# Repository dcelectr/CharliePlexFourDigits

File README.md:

# CharliePlexFourDigits
Four Digit (5 x 7 + 1dp) LED Matrices for use with the Adafruit 16x9 Charlieplexed PWM LED Matrix Driver - IS31FL3731 (Adafruit Product ID: 2946).
Up to four units can be used on the same I2C bus (addresses 0x74, 0x75, 0x76, and 0x77).

# To do
Arduino library.

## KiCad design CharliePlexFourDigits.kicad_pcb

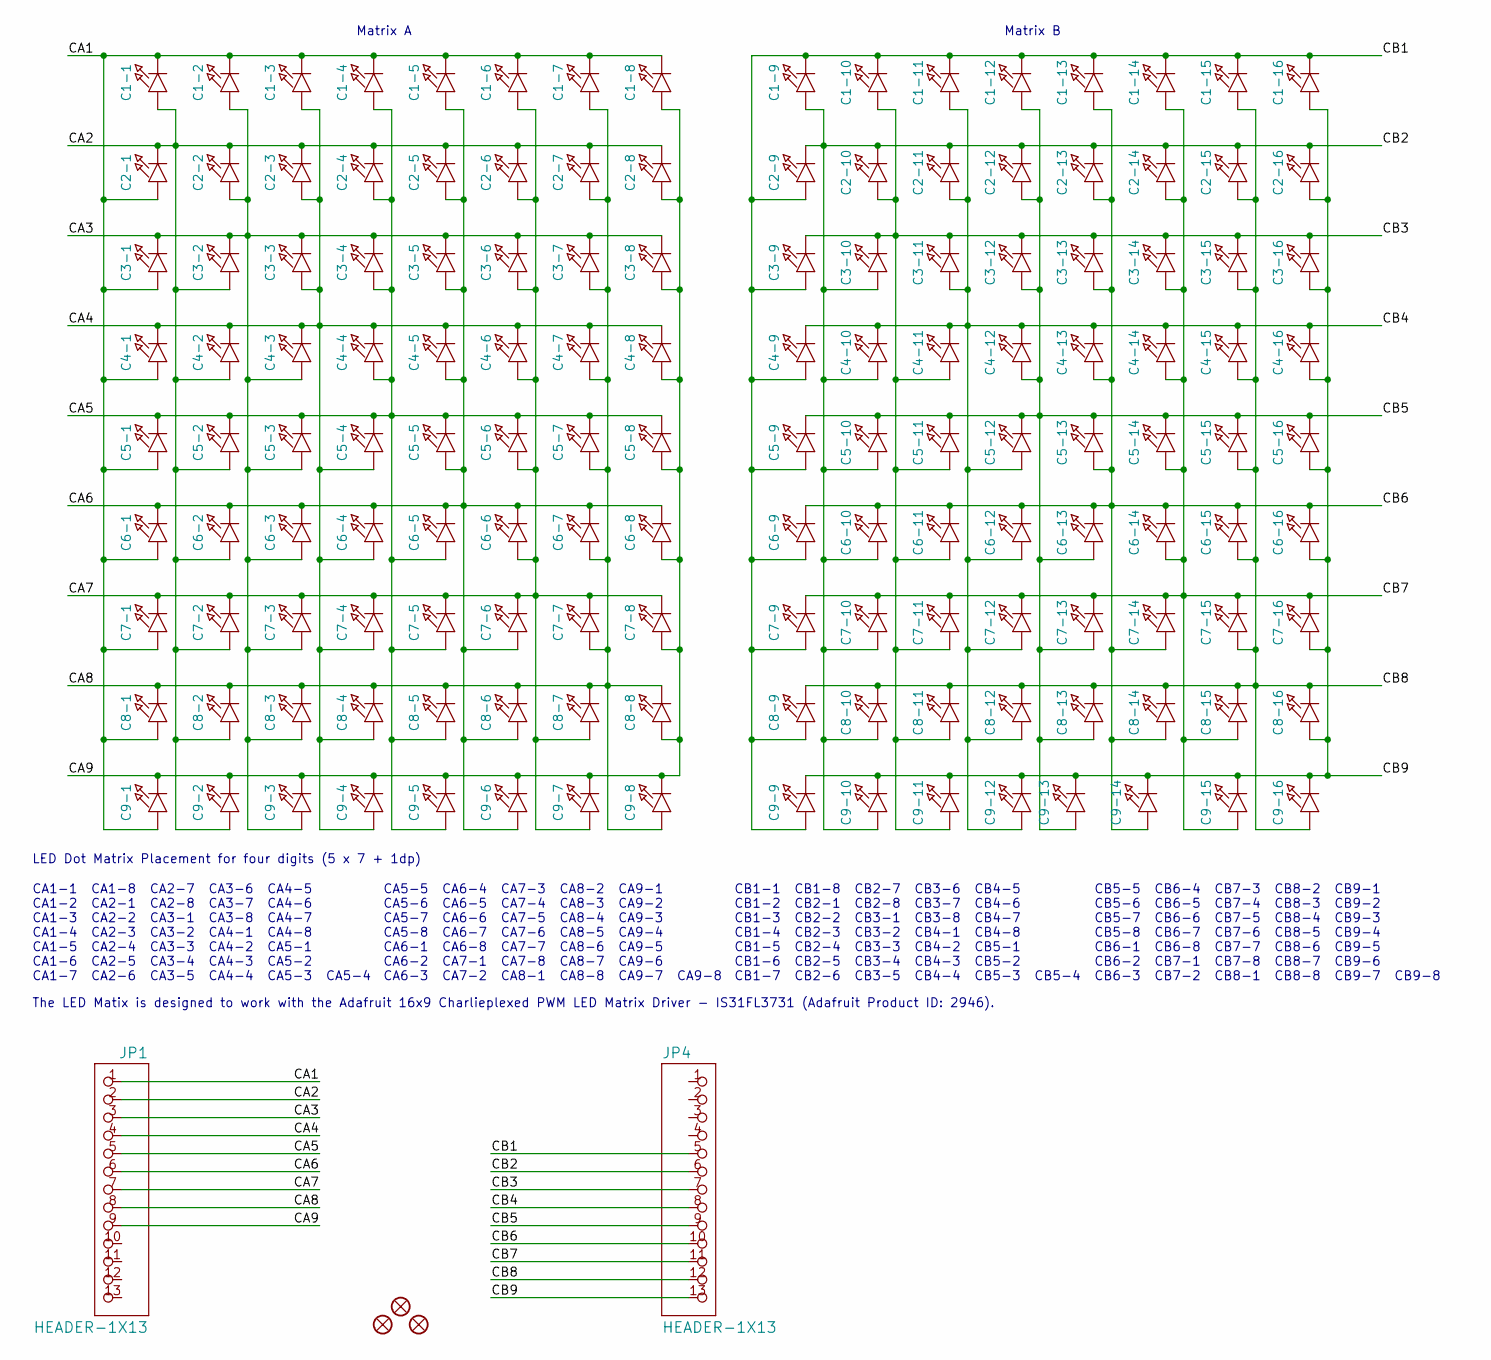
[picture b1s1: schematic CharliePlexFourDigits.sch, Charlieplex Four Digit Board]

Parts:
C1-1, C1-2, C1-3, C1-4, C1-5, C1-6, C1-7, C1-8, C1-9, C1-10, C1-11, C1-12, C1-13, C1-14, C1-15, C1-16, C2-1, C2-2, C2-3, C2-4, C2-5, C2-6, C2-7, C2-8, C2-9, C2-10, C2-11, C2-12, C2-13, C2-14, C2-15, C2-16, C3-1, C3-2, C3-3, C3-4, C3-5, C3-6, C3-7, C3-8, C3-9, C3-10, C3-11, C3-12, C3-13, C3-14, C3-15, C3-16, C4-1, C4-2, C4-3, C4-4, C4-5, C4-6, C4-7, C4-8, C4-9, C4-10, C4-11, C4-12, C4-13, C4-14, C4-15, C4-16, C5-1, C5-2, C5-3, C5-4, C5-5, C5-6, C5-7, C5-8, C5-9, C5-10, C5-11, C5-12, C5-13, C5-14, C5-15, C5-16, C6-1, C6-2, C6-3, C6-4, C6-5, C6-6, C6-7, C6-8, C6-9, C6-10, C6-11, C6-12, C6-13, C6-14, C6-15, C6-16, C7-1, C7-2, C7-3, C7-4, C7-5, C7-6, C7-7, C7-8, C7-9, C7-10, C7-11, C7-12, C7-13, C7-14, C7-15, C7-16, C8-1, C8-2, C8-3, C8-4, C8-5, C8-6, C8-7, C8-8, C8-9, C8-10, C8-11, C8-12, C8-13, C8-14, C8-15, C8-16, C9-1, C9-2, C9-3, C9-4, C9-5, C9-6, C9-7, C9-8, C9-9, C9-10, C9-11, C9-12, C9-13, C9-14, C9-15, C9-16: LED0603_NOOUTLINE; CHIPLED_0603_NOOUTLINE
FID1, FID2, FID3: FIDUCIAL\"\"; FIDUCIAL_1MM
JP1, JP4: HEADER-1X13; 1X13_ROUND_70

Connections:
/CA1: C1-1.C, C1-2.C, C1-3.C, C1-4.C, C1-5.C, C1-6.C, C1-7.C, C1-8.C, C2-1.A, C3-1.A, C4-1.A, C5-1.A, C6-1.A, C7-1.A, C8-1.A, C9-1.A, JP1.1
/CA2: C1-1.A, C2-1.C, C2-2.C, C2-3.C, C2-4.C, C2-5.C, C2-6.C, C2-7.C, C2-8.C, C3-2.A, C4-2.A, C5-2.A, C6-2.A, C7-2.A, C8-2.A, C9-2.A, JP1.2
/CA3: C1-2.A, C2-2.A, C3-1.C, C3-2.C, C3-3.C, C3-4.C, C3-5.C, C3-6.C, C3-7.C, C3-8.C, C4-3.A, C5-3.A, C6-3.A, C7-3.A, C8-3.A, C9-3.A, JP1.3
/CA4: C1-3.A, C2-3.A, C3-3.A, C4-1.C, C4-2.C, C4-3.C, C4-4.C, C4-5.C, C4-6.C, C4-7.C, C4-8.C, C5-4.A, C6-4.A, C7-4.A, C8-4.A, C9-4.A, JP1.4
/CA5: C1-4.A, C2-4.A, C3-4.A, C4-4.A, C5-1.C, C5-2.C, C5-3.C, C5-4.C, C5-5.C, C5-6.C, C5-7.C, C5-8.C, C6-5.A, C7-5.A, C8-5.A, C9-5.A, JP1.5
/CA6: C1-5.A, C2-5.A, C3-5.A, C4-5.A, C5-5.A, C6-1.C, C6-2.C, C6-3.C, C6-4.C, C6-5.C, C6-6.C, C6-7.C, C6-8.C, C7-6.A, C8-6.A, C9-6.A, JP1.6
/CA7: C1-6.A, C2-6.A, C3-6.A, C4-6.A, C5-6.A, C6-6.A, C7-1.C, C7-2.C, C7-3.C, C7-4.C, C7-5.C, C7-6.C, C7-7.C, C7-8.C, C8-7.A, C9-7.A, JP1.7
/CA8: C1-7.A, C2-7.A, C3-7.A, C4-7.A, C5-7.A, C6-7.A, C7-7.A, C8-1.C, C8-2.C, C8-3.C, C8-4.C, C8-5.C, C8-6.C, C8-7.C, C8-8.C, C9-8.A, JP1.8
/CA9: C1-8.A, C2-8.A, C3-8.A, C4-8.A, C5-8.A, C6-8.A, C7-8.A, C8-8.A, C9-1.C, C9-2.C, C9-3.C, C9-4.C, C9-5.C, C9-6.C, C9-7.C, C9-8.C, JP1.9
/CB1: C1-9.C, C1-10.C, C1-11.C, C1-12.C, C1-13.C, C1-14.C, C1-15.C, C1-16.C, C2-9.A, C3-9.A, C4-9.A, C5-9.A, C6-9.A, C7-9.A, C8-9.A, C9-9.A, JP4.5
/CB2: C1-9.A, C2-9.C, C2-10.C, C2-11.C, C2-12.C, C2-13.C, C2-14.C, C2-15.C, C2-16.C, C3-10.A, C4-10.A, C5-10.A, C6-10.A, C7-10.A, C8-10.A, C9-10.A, JP4.6
/CB3: C1-10.A, C2-10.A, C3-9.C, C3-10.C, C3-11.C, C3-12.C, C3-13.C, C3-14.C, C3-15.C, C3-16.C, C4-11.A, C5-11.A, C6-11.A, C7-11.A, C8-11.A, C9-11.A, JP4.7
/CB4: C1-11.A, C2-11.A, C3-11.A, C4-9.C, C4-10.C, C4-11.C, C4-12.C, C4-13.C, C4-14.C, C4-15.C, C4-16.C, C5-12.A, C6-12.A, C7-12.A, C8-12.A, C9-12.A, JP4.8
/CB5: C1-12.A, C2-12.A, C3-12.A, C4-12.A, C5-9.C, C5-10.C, C5-11.C, C5-12.C, C5-13.C, C5-14.C, C5-15.C, C5-16.C, C6-13.A, C7-13.A, C8-13.A, C9-13.A, JP4.9
/CB6: C1-13.A, C2-13.A, C3-13.A, C4-13.A, C5-13.A, C6-9.C, C6-10.C, C6-11.C, C6-12.C, C6-13.C, C6-14.C, C6-15.C, C6-16.C, C7-14.A, C8-14.A, C9-14.A, JP4.10
/CB7: C1-14.A, C2-14.A, C3-14.A, C4-14.A, C5-14.A, C6-14.A, C7-9.C, C7-10.C, C7-11.C, C7-12.C, C7-13.C, C7-14.C, C7-15.C, C7-16.C, C8-15.A, C9-15.A, JP4.11
/CB8: C1-15.A, C2-15.A, C3-15.A, C4-15.A, C5-15.A, C6-15.A, C7-15.A, C8-9.C, C8-10.C, C8-11.C, C8-12.C, C8-13.C, C8-14.C, C8-15.C, C8-16.C, C9-16.A, JP4.12
/CB9: C1-16.A, C2-16.A, C3-16.A, C4-16.A, C5-16.A, C6-16.A, C7-16.A, C8-16.A, C9-9.C, C9-10.C, C9-11.C, C9-12.C, C9-13.C, C9-14.C, C9-15.C, C9-16.C, JP4.13

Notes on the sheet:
Matrix A
Matrix B
CA1-1 CA1-8 CA2-7 CA3-6 CA4-5 CA1-2 CA2-1 CA2-8 CA3-7 CA4-6 CA1-3 CA2-2 CA3-1 CA3-8 CA4-7 CA1-4 CA2-3 CA3-2 CA4-1 CA4-8 CA1-5 CA2-4 CA3-3 CA4-2 CA5-1 CA1-6 CA2-5 CA3-4 CA4-3 CA5-2 CA1-7 CA2-6 CA3-5 CA4-4 CA5-3 CA5-4
CA5-5 CA6-4 CA7-3 CA8-2 CA9-1 CA5-6 CA6-5 CA7-4 CA8-3 CA9-2 CA5-7 CA6-6 CA7-5 CA8-4 CA9-3 CA5-8 CA6-7 CA7-6 CA8-5 CA9-4 CA6-1 CA6-8 CA7-7 CA8-6 CA9-5 CA6-2 CA7-1 CA7-8 CA8-7 CA9-6 CA6-3 CA7-2 CA8-1 CA8-8 CA9-7 CA9-8
CB1-1 CB1-8 CB2-7 CB3-6 CB4-5 CB1-2 CB2-1 CB2-8 CB3-7 CB4-6 CB1-3 CB2-2 CB3-1 CB3-8 CB4-7 CB1-4 CB2-3 CB3-2 CB4-1 CB4-8 CB1-5 CB2-4 CB3-3 CB4-2 CB5-1 CB1-6 CB2-5 CB3-4 CB4-3 CB5-2 CB1-7 CB2-6 CB3-5 CB4-4 CB5-3 CB5-4
CB5-5 CB6-4 CB7-3 CB8-2 CB9-1 CB5-6 CB6-5 CB7-4 CB8-3 CB9-2 CB5-7 CB6-6 CB7-5 CB8-4 CB9-3 CB5-8 CB6-7 CB7-6 CB8-5 CB9-4 CB6-1 CB6-8 CB7-7 CB8-6 CB9-5 CB6-2 CB7-1 CB7-8 CB8-7 CB9-6 CB6-3 CB7-2 CB8-1 CB8-8 CB9-7 CB9-8
The LED Matix is designed to work with the Adafruit 16x9 Charlieplexed PWM LED Matrix Driver - IS31FL3731 (Adafruit Product ID: 2946).
LED Dot Matrix Placement for four digits (5 x 7 + 1dp)

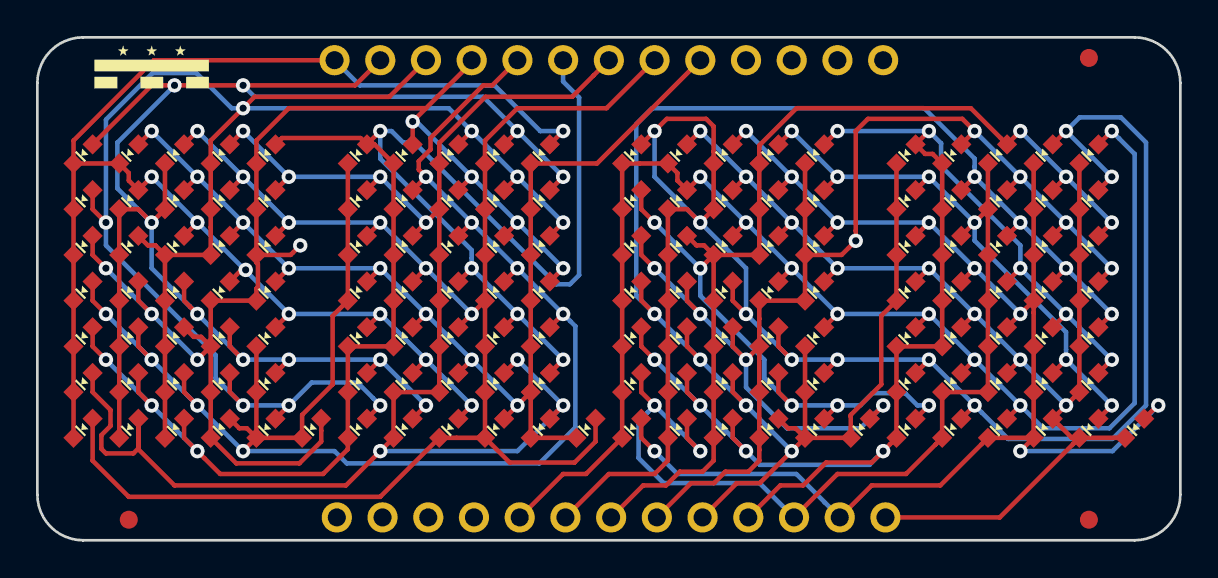
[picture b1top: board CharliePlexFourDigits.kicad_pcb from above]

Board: 2 copper layers, 63.5 x 27.9 mm, 149 parts (0 on the bottom side), 18 nets.

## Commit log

2020-12-26 Added Screenshots
2020-12-26 Added PDF Schematic
